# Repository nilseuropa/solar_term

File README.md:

# SolarTerm

SolarTerm is a family of handheld enclosures for running
[SolarOS](https://github.com/nilseuropa/solar_os). Each design combines an
ESP32-S3 display board with a Rii 518BT Mini Bluetooth keyboard, battery power,
and optional microSD storage.

Two board families are supported:

- **SolarTerm RLCD** uses the reflective
  [Waveshare ESP32-S3-RLCD-4.2](https://docs.waveshare.com/ESP32-S3-RLCD-4.2).
- **SolarTerm IPS** uses the color, capacitive-touch Freenove ESP32-S3 Display
  4.0-inch (FNK0104S).

> [!IMPORTANT]
> The RLCD and IPS enclosures are board-specific. Their printed parts, battery
> arrangements, connectors, and pin assignments are not interchangeable.

SolarOS names the Waveshare configuration `solar_term` and the Freenove
configuration `freenove_esp32_s3_display_4_0`.

## Build the enclosure

Three enclosure designs are included:

- [IPS enclosure](doc/build_ips.md) — the enclosure for the Freenove 4.0-inch
  IPS board.
- [ATA F&E RLCD enclosure](doc/build_ata.md) — the multipart Waveshare design,
  with threaded inserts and an optional protective acrylic window.
- [Original RLCD enclosure](doc/build_nils.md) — the simpler Waveshare
  proof-of-concept print-and-screw design.

Read the selected build guide before ordering or printing parts. The display is
fragile and must not be used as leverage while inserting a cable, battery, or
enclosure part.

## Install SolarOS

For a first installation or recovery, use the
[SolarOS Web Flasher](https://solar-os.eu/flasher.html) in Chrome or Edge on a
desktop computer. Connect the board with a data-capable USB cable and select
the entry that matches the enclosure:

| Enclosure | Board in the Flasher |
| --- | --- |
| SolarTerm RLCD | SolarTerm (Waveshare ESP32-S3-RLCD-4.2) |
| SolarTerm IPS | Freenove ESP32-S3 Display 4.0-inch (FNK0104S) |

The Flasher downloads and verifies the selected official release before
installing it. Follow its board-specific download-mode instructions and keep
the USB cable connected until installation completes.

To build or flash SolarOS from source instead, follow the
[SolarOS quick start](https://solar-os.eu/quick-start.html#build-and-flash-from-source).
It lists the required tools, PlatformIO environments, upload commands, and
troubleshooting steps for supported boards.

## First boot

1. Power the board and wait for the SolarOS shell.
2. Turn on the Rii keyboard with its side switch.
3. Press the pairing button on the back of the keyboard.
4. Hold the board's SolarOS **KEY** button for about two seconds: **KEY** on the
   Waveshare board, or **BOOT** on the Freenove board after SolarOS has started.
   Release it when the keyboard icon changes to its pairing or scanning state.
   The display shell does not print a pairing message.
5. Wait for the keyboard to connect, then type at the shell.

SolarOS remembers the keyboard and reconnects on later boots. A long press of
**KEY** starts pairing again; a second long press while pairing cancels it.

## Optional microSD card

SolarTerm works without a card. To add storage, format a microSD card as FAT32
and insert it while SolarTerm is powered off. SolarOS mounts it at `/sdcard`
during boot.

```text
sd status
df
```

If the card is detected but not mounted, run `sd lsblk` and then `sd mount`.

## Update SolarOS over the air

Run `wifi` and connect to a network, then check for and install the latest
compatible SolarOS release:

```text
ota check
ota upgrade
```

SolarOS verifies the image, writes it to the inactive firmware slot, and
reboots into it. Keep the device powered until the upgrade finishes.

## Expansion cards

The Waveshare RLCD board has a 2 × 8 expansion header with 2.54 mm pitch.
SolarTerm cards use 3.3 V logic and follow the SolarOS pin assignments. They do
not fit the Freenove IPS board. See the
[SolarTerm expansion-card guide](expansions/README.md) before designing or
connecting a card.

The repository currently includes the [SolarLink radio expansion](expansions/solarlink/README.md),
with Autodesk EAGLE source, Gerber files, build information, and a photograph
of the functional prototype.

## More information

Visit [solar-os.eu](https://solar-os.eu/) for SolarOS documentation, tutorials,
and project updates.

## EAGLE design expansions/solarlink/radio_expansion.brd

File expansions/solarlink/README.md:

# SolarLink radio expansion

SolarLink adds two sub-GHz radios to SolarTerm:

- one `RFM69HW-868S2`;
- one `RFM95W-915S2`.

Both radios share one SPI bus. Each radio has its own chip-select signal and
antenna. The pictured prototype has been built and validated as functional with
the Waveshare ESP32-S3-RLCD-4.2 and SolarOS.

## Single-layer construction

SolarLink routes all tracks on one copper layer. This makes the PCB easy to
produce at home.

`R1` is a 0 Ω wire bridge, not a resistor. It carries MOSI across another track
without adding a second copper layer. Fit `R1` with a short insulated wire, as
shown in the photograph.

The PCB is 76.2 × 48.26 mm. It connects to the Waveshare board with a 2 × 8 male
header on a 2.54 mm pitch.

## Parts

- 1 × single-layer SolarLink PCB
- 1 × `RFM69HW-868S2` module
- 1 × `RFM95W-915S2` module
- 1 × 2 × 8 male header, 2.54 mm pitch
- 1 × short insulated wire for the `R1` bridge
- 1 × antenna for each fitted radio module

Use antennas for the frequency bands of the fitted modules.

## Electrical connections

| SolarTerm signal | SolarLink function |
| --- | --- |
| 3V3 | RFM69HW and RFM95W supply |
| GND | Radio ground |
| GPIO1 | Shared SPI SCK |
| GPIO2 | Shared SPI MOSI |
| GPIO3 | Shared SPI MISO |
| GPIO43 / TXD | RFM69HW NSS/chip select |
| GPIO44 / RXD | RFM95W NSS/chip select |
| GPIO17 | RFM95W reset |

The RFM69 reset signal and all DIO/IRQ signals are unconnected. SolarOS polls
the radio modules, so no IRQ connection is required.

GPIO43 and GPIO44 belong to `uart0` at boot. Use the display shell and detach
`uart0` before attaching either radio.

## Design and fabrication files

| Path | Contents |
| --- | --- |
| [`radio_expansion.sch`](radio_expansion.sch) | Autodesk EAGLE 7.7 schematic |
| [`radio_expansion.brd`](radio_expansion.brd) | Autodesk EAGLE 7.7 PCB layout |
| [`eagle.epf`](eagle.epf) | EAGLE project settings |
| [`gerber/`](gerber/) | Gerber and Excellon fabrication files |

## SolarOS setup

Start from the display shell and inspect the available resources:

```text
expansion layout
expansion status
expansion drivers
```

Detach `uart0`, create the shared SPI bus, and attach both radios:

```text
expansion bus detach uart0
expansion bus create spi solarlink host=spi3 sclk=gpio1 mosi=gpio2 miso=gpio3 cs=gpio43 cs=gpio44
expansion attach rfm69h radio69 spi=solarlink cs=gpio43
expansion attach rfm95 radio95 spi=solarlink cs=gpio44 reset=gpio17
radio status radio69
radio status radio95
```

Attach only the radio modules fitted to the card. Connect the antennas before
transmitting. Use frequencies and power levels allowed in your region.

To detach the radios and restore `uart0`:

```text
expansion detach radio95
expansion detach radio69
expansion bus remove solarlink
expansion bus attach uart0
```

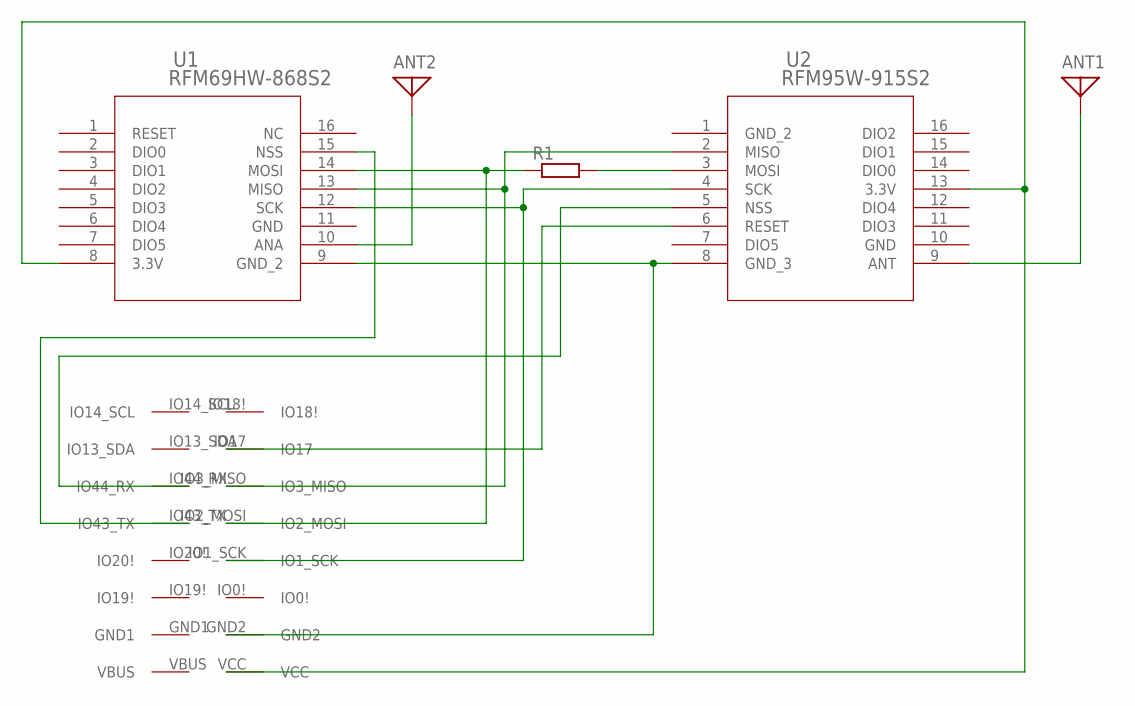
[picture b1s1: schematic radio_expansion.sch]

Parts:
ANT1, ANT2: ANTENNA; PAD-01
R1: R-EU_M5923; M5923
U1: RFM69HW-868S2; RFM69HW_S2_HRF
U2: RFM95W-915S2; IC16_RFM95W-915S2_RFS
U$1: SOLARTERM_EXP; CONN

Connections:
GND: U1.9 (GND_2), U2.8 (GND_3), U$1.GND2
MISO: U1.13 (MISO), U2.2 (MISO), U$1.IO3_MISO
MOSI: R1.1, R1.2, U1.14 (MOSI), U2.3 (MOSI), U$1.IO2_MOSI
unnamed: ANT2.1, U1.10 (ANA)
unnamed: ANT1.1, U2.9 (ANT)
RESET: U2.6 (RESET), U$1.IO17
SCK: U1.12 (SCK), U2.4 (SCK), U$1.IO1_SCK
SEL69: U1.15 (NSS), U$1.IO43_TX
SEL95: U2.5 (NSS), U$1.IO44_RX
VCC: U1.8 (3.3V), U2.13 (3.3V), U$1.VCC

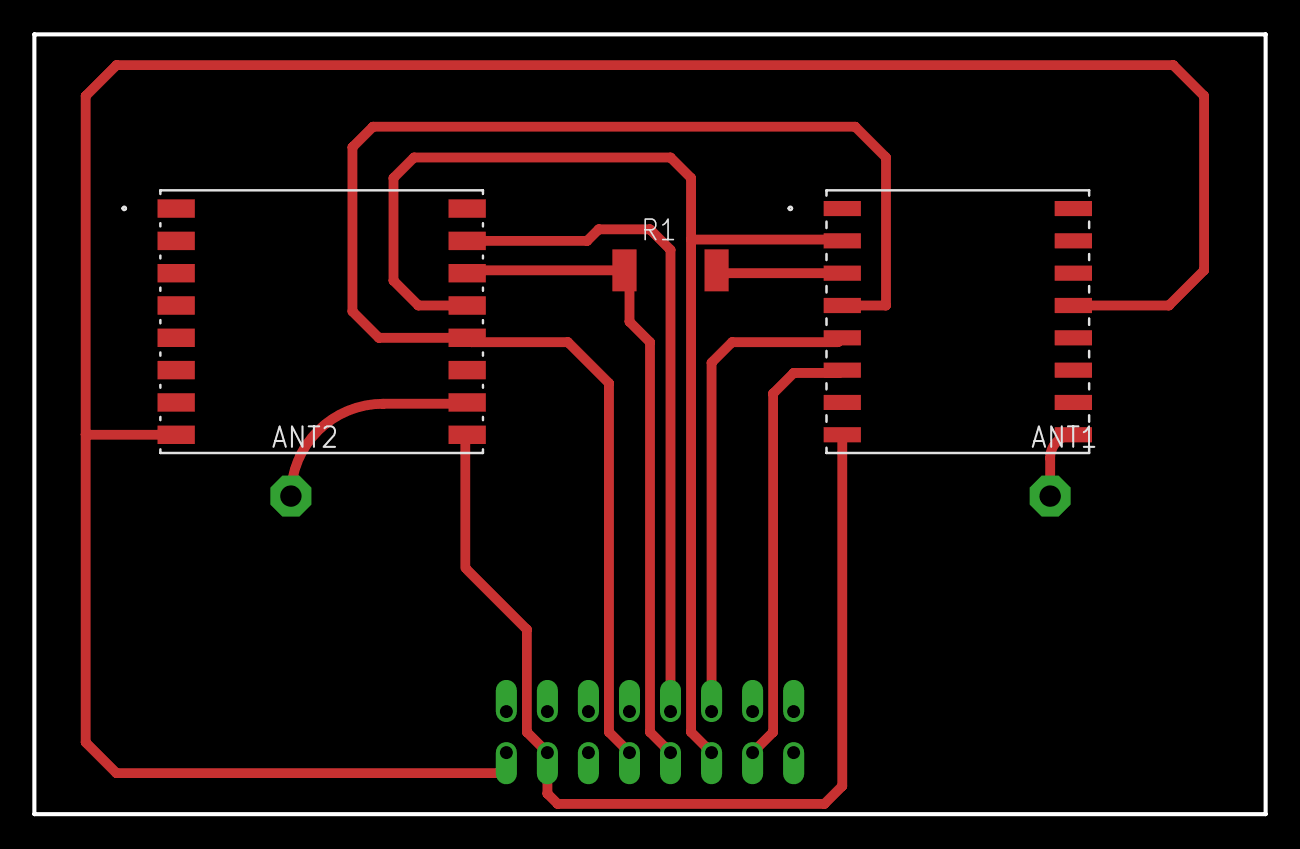
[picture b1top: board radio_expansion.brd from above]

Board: 2 copper layers, 76.2 x 48.3 mm, 6 parts (0 on the bottom side), 10 nets.

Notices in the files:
parts and their libraries:
COPYRIGHT: Copyright (C) 2026 Ultra Librarian. All rights reserved.
